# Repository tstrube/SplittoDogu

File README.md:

# SplittoDogu
QMK firmware for split keyboard with screens and encoders

This is a split keyboard with encoders for arrow keys, mouse wheels, page up/down, and undo/redo.
One of the two screens shows the active layer and status of Num and Caps. The other screen is for Bongo Cat...

It's also possible to use one side only. (Garming or Macro Keyboard)

Optional components: screens, encoder, buttons...

## Layouts
There are two nearly identical default layouts. One for Windows and the other for MAC.
The differences are key combinations for undo/redo and other hotkeys.

Next is a layer for gaming, which shifts most buttons on the left half to the right by one key.
This is moves WASD to the optimal position.

The last layer FN is for F1 to F12, arrow keys, and the keypad.

## PCB
The PCB can be used for both sides. It's possible to use one half without the other.
So select which side a board is used for, bridge the jumper points under the OLED screen.
JP_L1 to JP_L6 for the left side, JP_R1 to JP_R6 for the right.
The Elite-C must be flipped depending on the side. (See images)

## Case
The case is a simple sandwich case with a clear part covering the chip and screen.
The main case uses 8mm standoffs, while the clear part uses 11mm. (See BOM)

## BOM
A list with all parts used and their approximate price as of March 2022.

## Crypto Donations

- **BTC:** bc1qqa9skjw0av0dnpzl53dhapgllw9nxpr3e3ncg6
- **DOGE:** D6Skk3K4H8KZWc7WcG69Ki5mkXc3f8pscc
- **ETH:** 0x7370eD840A690010eEF5726D71eEa54a9F45A202
- **SOL:** FipyS8kETFE8XRMkDez1nRRNe1n94Etws15UQfvzRsgg
- **XCH:** xch10t2jmnrnq8295pxqdtvn4pp5dgdcm7aar5usz0e4e57xyyjegtuqxwtq9z

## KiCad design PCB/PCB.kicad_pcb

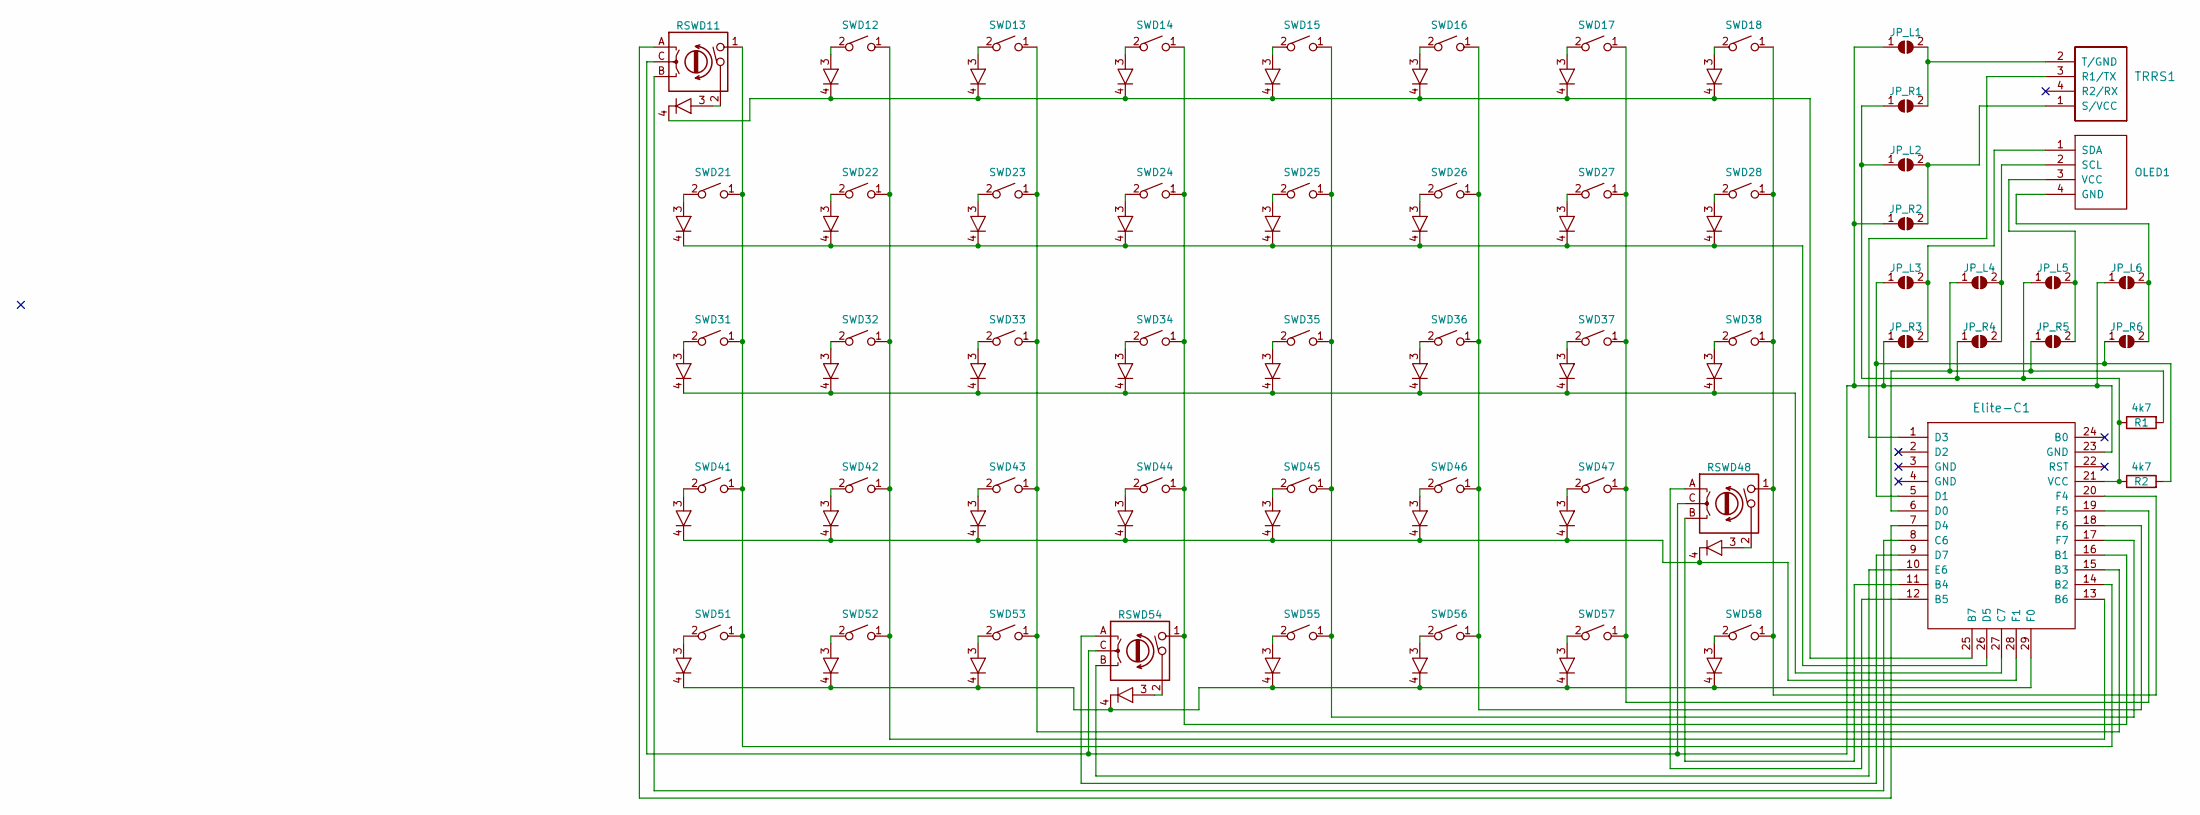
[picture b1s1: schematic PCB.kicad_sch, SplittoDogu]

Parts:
Elite-C1: Elite-C
JP_L1, JP_L2, JP_L3, JP_L4, JP_L5, JP_L6: SolderJumper_Open
JP_R1, JP_R2, JP_R3, JP_R4, JP_R5, JP_R6: SolderJumper_Open
OLED1: OLED
R1, R2: 4k7; R_Axial_DIN0207_L6.3mm_D2.5mm_P10.16mm_Horizontal
RSWD11, RSWD48, RSWD54: RotaryEncoder_Switch_Diode
SWD12, SWD13, SWD14, SWD15, SWD16, SWD17, SWD18, SWD21, SWD22, SWD23, SWD24, SWD25, SWD26, SWD27, SWD28, SWD31, SWD32, SWD33, SWD34, SWD35, SWD36, SWD37, SWD38, SWD41, SWD42, SWD43, SWD44, SWD45, SWD46, SWD47, SWD51, SWD52, SWD53, SWD55, SWD56, SWD57, SWD58: MX_Diode; MX
TRRS1: TRRS; TRRS-PJ-320A

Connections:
unnamed: Elite-C1.1 (D3), TRRS1.3 (R1/TX)
unnamed: Elite-C1.5 (D1), JP_L3.1, JP_R6.1, R2.2
unnamed: Elite-C1.6 (D0), JP_L4.1, JP_R5.1, R1.2
unnamed: Elite-C1.7 (D4), RSWD11.A
unnamed: Elite-C1.8 (C6), RSWD11.B
unnamed: Elite-C1.9 (D7), RSWD54.A
unnamed: Elite-C1.10 (E6), RSWD54.B
unnamed: Elite-C1.11 (B4), RSWD48.B
unnamed: Elite-C1.12 (B5), RSWD48.A
unnamed: Elite-C1.13 (B6), SWD12.1, SWD22.1, SWD32.1, SWD42.1, SWD52.1
unnamed: Elite-C1.14 (B2), RSWD11.1, SWD21.1, SWD31.1, SWD41.1, SWD51.1
unnamed: Elite-C1.15 (B3), SWD13.1, SWD23.1, SWD33.1, SWD43.1, SWD53.1
unnamed: Elite-C1.16 (B1), RSWD54.1, SWD14.1, SWD24.1, SWD34.1, SWD44.1
unnamed: Elite-C1.17 (F7), SWD15.1, SWD25.1, SWD35.1, SWD45.1, SWD55.1
unnamed: Elite-C1.18 (F6), SWD16.1, SWD26.1, SWD36.1, SWD46.1, SWD56.1
unnamed: Elite-C1.19 (F5), SWD17.1, SWD27.1, SWD37.1, SWD47.1, SWD57.1
unnamed: Elite-C1.20 (F4), RSWD48.1, SWD18.1, SWD28.1, SWD38.1, SWD58.1
unnamed: Elite-C1.21 (VCC), JP_L2.1, JP_L5.1, JP_R1.1, JP_R4.1, R1.1, R2.1
unnamed: Elite-C1.23 (GND), JP_L1.1, JP_L6.1, JP_R2.1, JP_R3.1, RSWD11.C, RSWD48.C, RSWD54.C
unnamed: Elite-C1.25 (B7), RSWD11.4, SWD12.4, SWD13.4, SWD14.4, SWD15.4, SWD16.4, SWD17.4, SWD18.4
unnamed: Elite-C1.26 (D5), SWD21.4, SWD22.4, SWD23.4, SWD24.4, SWD25.4, SWD26.4, SWD27.4, SWD28.4
unnamed: Elite-C1.27 (C7), SWD31.4, SWD32.4, SWD33.4, SWD34.4, SWD35.4, SWD36.4, SWD37.4, SWD38.4
unnamed: Elite-C1.28 (F1), RSWD48.4, SWD41.4, SWD42.4, SWD43.4, SWD44.4, SWD45.4, SWD46.4, SWD47.4
unnamed: Elite-C1.29 (F0), RSWD54.4, SWD51.4, SWD52.4, SWD53.4, SWD55.4, SWD56.4, SWD57.4, SWD58.4
unnamed: JP_L1.2, JP_R1.2, TRRS1.2 (T/GND)
unnamed: JP_L2.2, JP_R2.2, TRRS1.1 (S/VCC)
unnamed: JP_L3.2, JP_R3.2, OLED1.1 (SDA)
unnamed: JP_L4.2, JP_R4.2, OLED1.2 (SCL)
unnamed: JP_L5.2, JP_R5.2, OLED1.3 (VCC)
unnamed: JP_L6.2, JP_R6.2, OLED1.4 (GND)
unnamed: RSWD11.2, RSWD11.3
unnamed: RSWD48.2, RSWD48.3
unnamed: RSWD54.2, RSWD54.3
unnamed: SWD12.2, SWD12.3
unnamed: SWD13.2, SWD13.3
unnamed: SWD14.2, SWD14.3
unnamed: SWD15.2, SWD15.3
unnamed: SWD16.2, SWD16.3
unnamed: SWD17.2, SWD17.3
unnamed: SWD18.2, SWD18.3
unnamed: SWD21.2, SWD21.3
unnamed: SWD22.2, SWD22.3
unnamed: SWD23.2, SWD23.3
unnamed: SWD24.2, SWD24.3
unnamed: SWD25.2, SWD25.3
unnamed: SWD26.2, SWD26.3
unnamed: SWD27.2, SWD27.3
unnamed: SWD28.2, SWD28.3
unnamed: SWD31.2, SWD31.3
unnamed: SWD32.2, SWD32.3
unnamed: SWD33.2, SWD33.3
unnamed: SWD34.2, SWD34.3
unnamed: SWD35.2, SWD35.3
unnamed: SWD36.2, SWD36.3
unnamed: SWD37.2, SWD37.3
unnamed: SWD38.2, SWD38.3
unnamed: SWD41.2, SWD41.3
unnamed: SWD42.2, SWD42.3
unnamed: SWD43.2, SWD43.3
unnamed: SWD44.2, SWD44.3
unnamed: SWD45.2, SWD45.3
unnamed: SWD46.2, SWD46.3
unnamed: SWD47.2, SWD47.3
unnamed: SWD51.2, SWD51.3
unnamed: SWD52.2, SWD52.3
unnamed: SWD53.2, SWD53.3
unnamed: SWD55.2, SWD55.3
unnamed: SWD56.2, SWD56.3
unnamed: SWD57.2, SWD57.3
unnamed: SWD58.2, SWD58.3

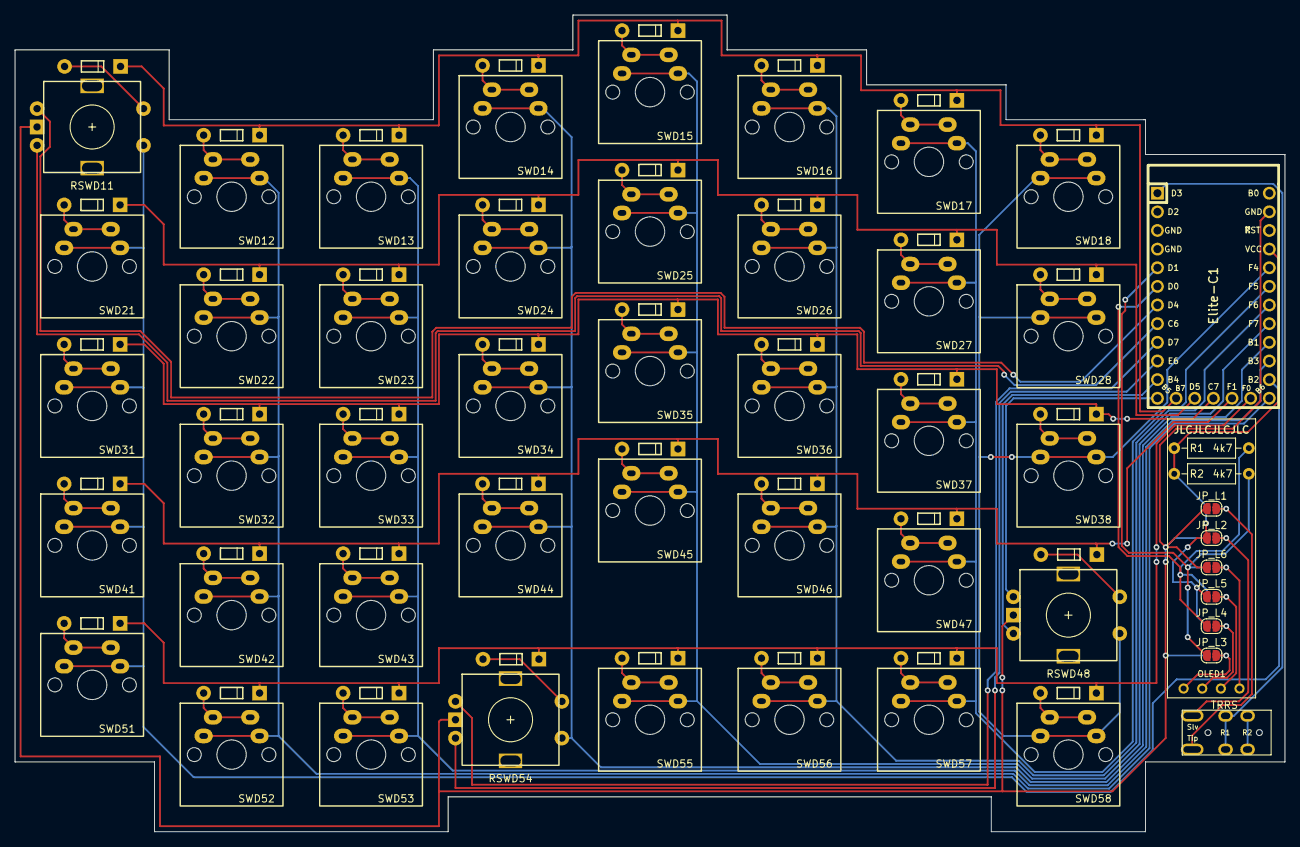
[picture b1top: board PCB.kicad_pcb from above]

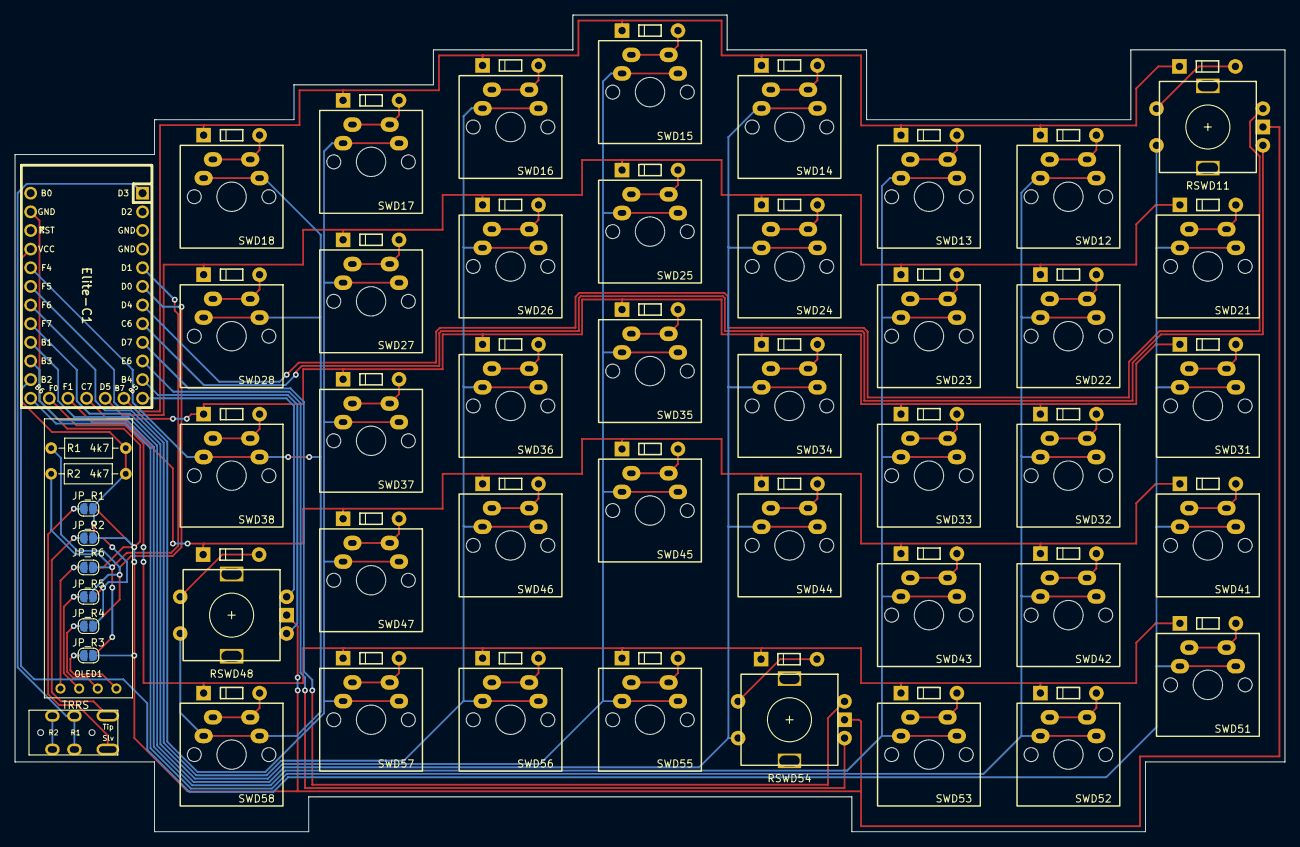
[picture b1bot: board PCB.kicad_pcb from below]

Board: 2 copper layers, 173.0 x 111.2 mm, 57 parts (6 on the bottom side), 70 nets.

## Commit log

2022-12-13 Init
2022-12-15 updated images
2022-12-15 switch plus return in numpad
2022-12-15 removed spaces from filenames
2022-12-15 update pcb image
2022-12-19 removed WIN key from Game layout
2022-12-23 removed some custom keycodes
2023-12-02 compatibility with new qmk version
2024-06-24 added donation addresses
